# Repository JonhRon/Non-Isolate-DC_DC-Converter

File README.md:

# DC-DC Converter
The Project that i do with my 4th year at University.

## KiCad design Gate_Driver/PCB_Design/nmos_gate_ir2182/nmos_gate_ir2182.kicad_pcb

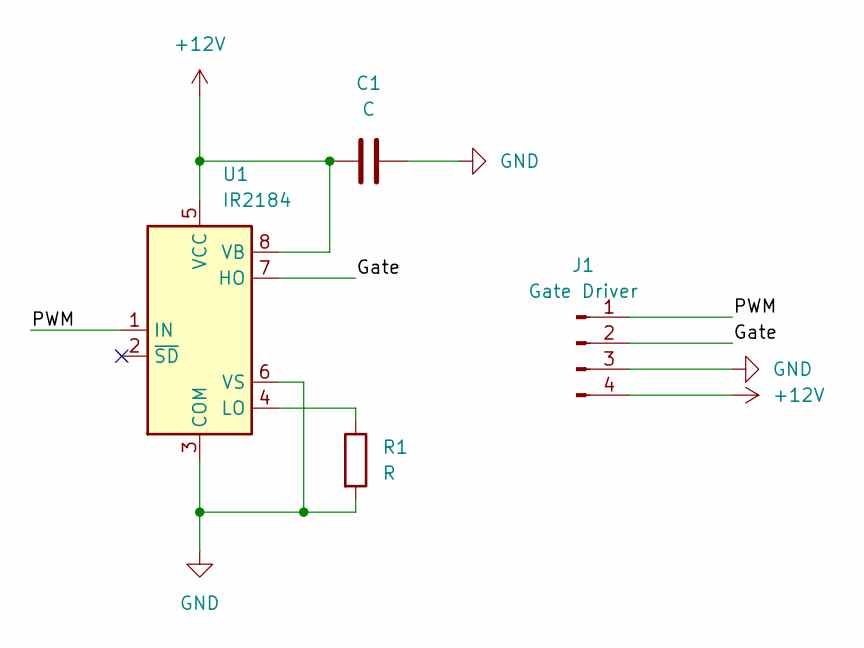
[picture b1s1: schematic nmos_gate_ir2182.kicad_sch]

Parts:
C1: C; C_0805_2012Metric_Pad1.18x1.45mm_HandSolder
J1: Gate Driver; PinHeader_1x04_P2.54mm_Vertical
R1: R; R_0805_2012Metric_Pad1.20x1.40mm_HandSolder
U1: IR2184; PowerIntegrations_SO-8

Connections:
+12V: C1.1, J1.4, U1.5 (VCC), U1.8 (VB)
/Gate: J1.2, U1.7 (HO)
/PWM: J1.1, U1.1 (IN)
GND: C1.2, J1.3, R1.2, U1.3 (COM), U1.6 (VS)
unnamed: R1.1, U1.4 (LO)

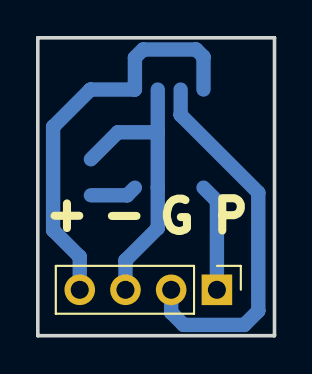
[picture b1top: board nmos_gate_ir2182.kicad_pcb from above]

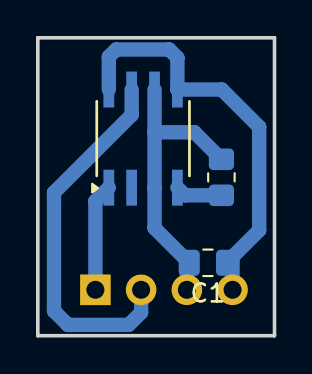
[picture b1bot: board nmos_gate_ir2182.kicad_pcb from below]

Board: 2 copper layers, 13.2 x 16.6 mm, 4 parts (3 on the bottom side), 5 nets.

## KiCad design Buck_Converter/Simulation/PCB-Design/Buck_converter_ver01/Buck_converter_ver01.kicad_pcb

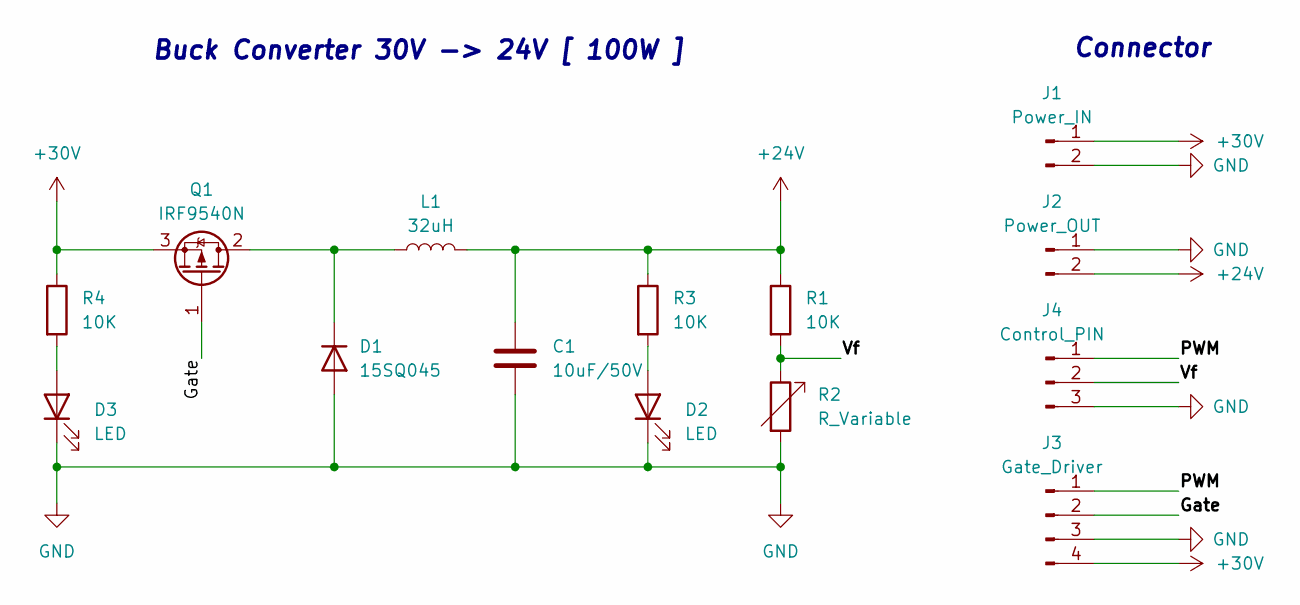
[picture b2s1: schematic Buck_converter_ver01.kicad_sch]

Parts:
C1: 10uF/50V; CP_Radial_D10.0mm_P3.50mm
D1: 15SQ045; D_P600_R-6_P12.70mm_Horizontal
D2, D3: LED; LED_D5.0mm
J1: Power_IN; TerminalBlock_bornier-2_P5.08mm
J2: Power_OUT; TerminalBlock_bornier-2_P5.08mm
J3: Gate_Driver; PinSocket_1x04_P2.54mm_Vertical
J4: Control_PIN; PinSocket_1x03_P2.54mm_Vertical
L1: 32uH; L_Wurth_WE-HCFT-2012_LeadDiameter1.5mm
Q1: IRF9540N; TO-220-3_Vertical
R1, R3, R4: 10K; R_0805_2012Metric_Pad1.20x1.40mm_HandSolder
R2: R_Variable; Potentiometer_Bourns_3296W_Vertical

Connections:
+24V: C1.1, J2.2, L1.2, R1.1, R3.1
+30V: J1.1, J3.4, Q1.3 (S), R4.1
/Gate: J3.2, Q1.1 (G)
/PWM: J3.1, J4.1
/Vf: J4.2, R1.2, R2.1
GND: C1.2, D1.2 (A), D2.1 (K), D3.1 (K), J1.2, J2.1, J3.3, J4.3, R2.2
unnamed: D1.1 (K), L1.1, Q1.2 (D)
unnamed: D2.2 (A), R3.2
unnamed: D3.2 (A), R4.2

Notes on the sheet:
Connector
Buck Converter 30V -> 24V [ 100W ]

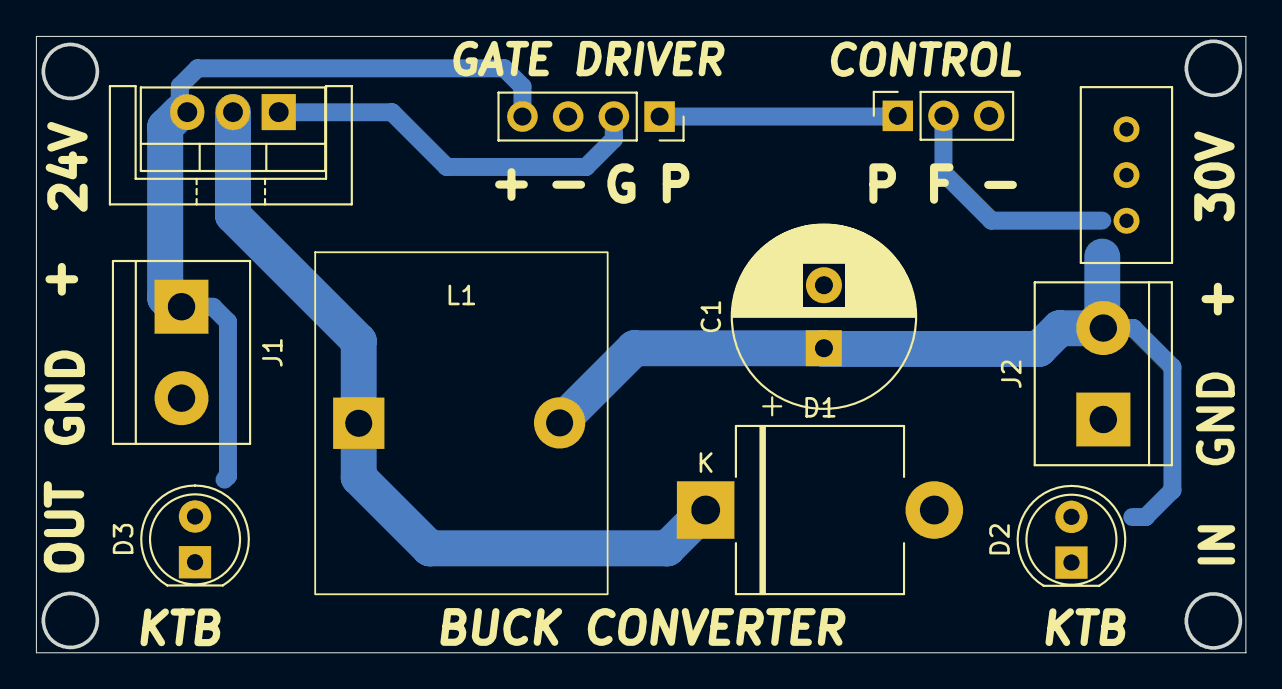
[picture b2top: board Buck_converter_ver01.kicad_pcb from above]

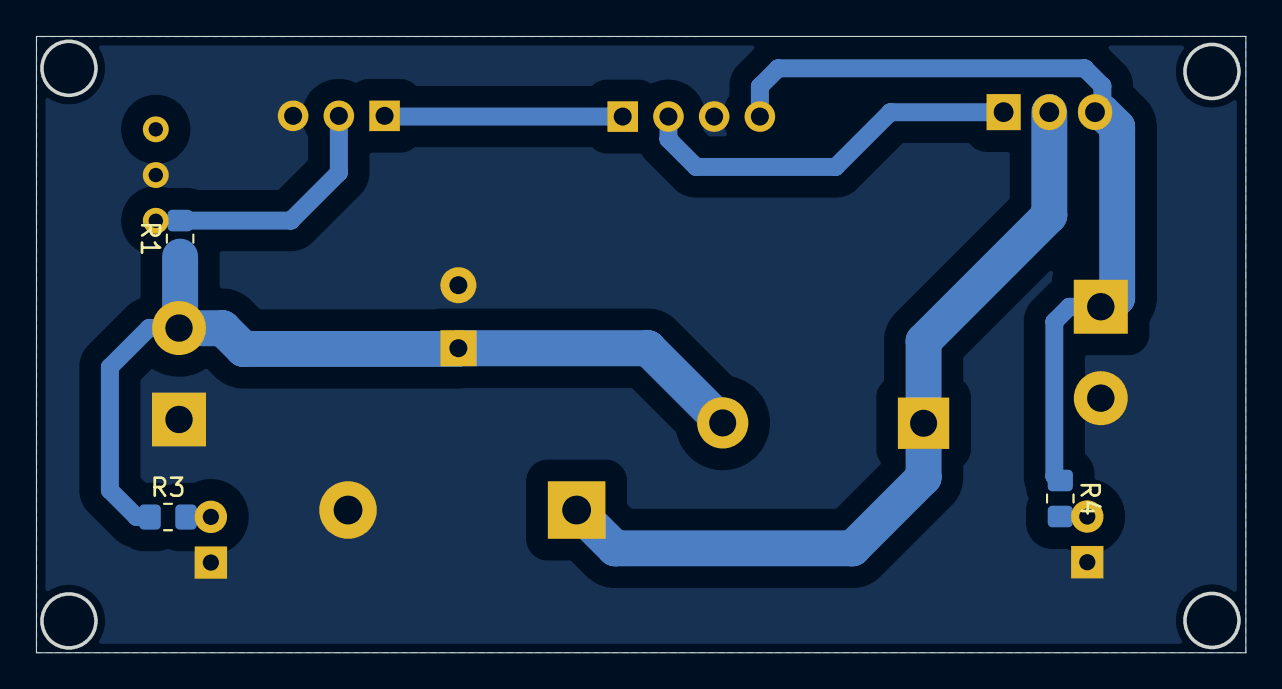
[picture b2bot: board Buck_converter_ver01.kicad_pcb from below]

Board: 2 copper layers, 67.2 x 34.2 mm, 14 parts (3 on the bottom side), 9 nets.

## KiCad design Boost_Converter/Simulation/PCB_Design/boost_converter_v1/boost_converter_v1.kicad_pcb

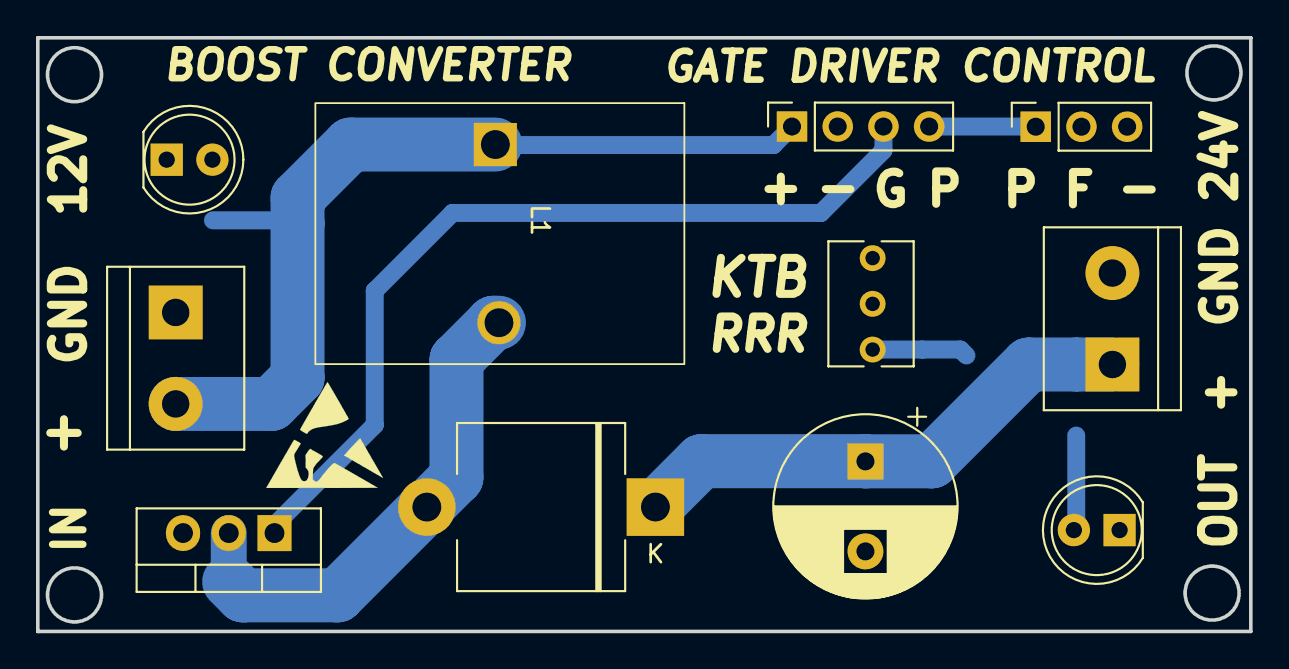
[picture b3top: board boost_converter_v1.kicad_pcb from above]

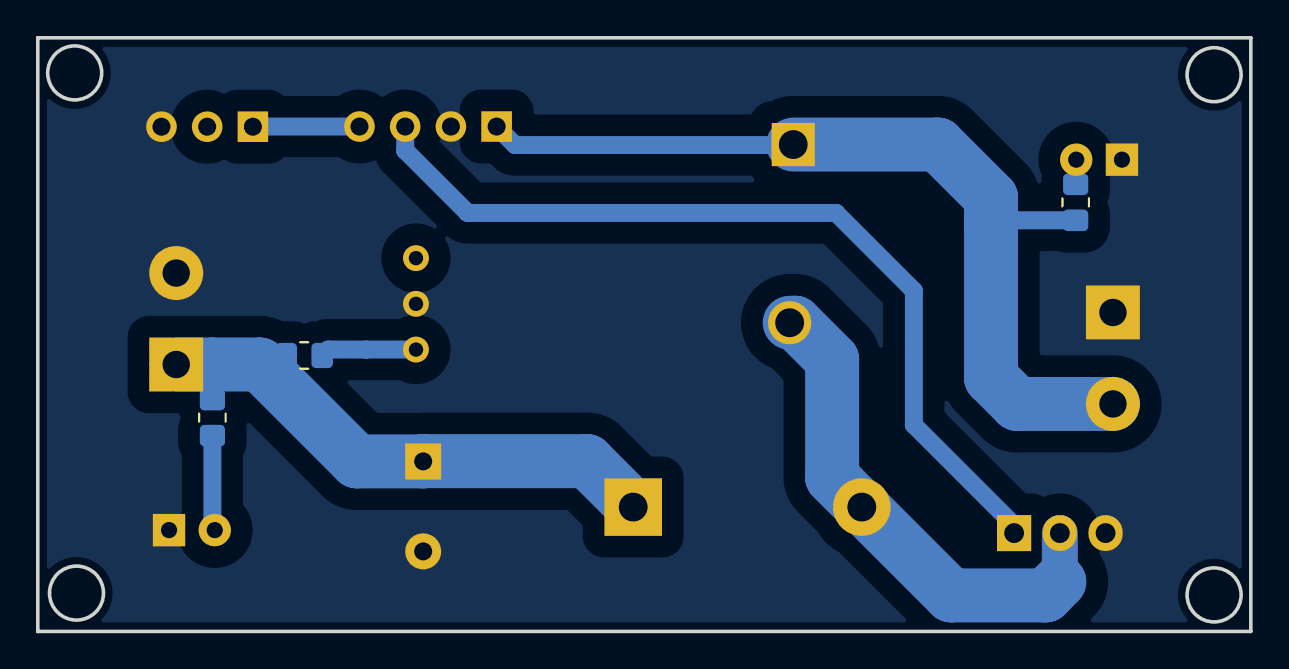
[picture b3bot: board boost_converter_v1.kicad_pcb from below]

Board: 2 copper layers, 67.4 x 33.0 mm, 14 parts (3 on the bottom side), 9 nets.

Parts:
C1: 100uF; CP_Radial_D10.0mm_P5.00mm
D1: 15SQ045; D_P600_R-6_P12.70mm_Horizontal
D2, D3: LED; LED_D5.0mm
J1: Power_IN; TerminalBlock_bornier-2_P5.08mm
J2: Power_OUT; TerminalBlock_bornier-2_P5.08mm
J3: Control; PinSocket_1x03_P2.54mm_Vertical
J4: Gate_Driver; PinSocket_1x04_P2.54mm_Vertical
L1: 20uH; L_Wurth_WE-HCFT-2012_LeadDiameter1.2mm
Q1: IRF540N; TO-220-3_Vertical
R1: 5K; R_0805_2012Metric_Pad1.20x1.40mm_HandSolder
R2, R3: 10K; R_0805_2012Metric_Pad1.20x1.40mm_HandSolder
R4: R_Variable; Potentiometer_Bourns_3266Y_Vertical

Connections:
+12V: J1.2, J4.1, L1.1, R1.1
+24V: C1.1, D1.1 (K), J2.1, R2.1, R3.1
/Gate: J4.3, Q1.1 (G)
/PWM: J3.1, J4.4
GND: C1.2, D2.1 (K), D3.1 (K), J1.1, J2.2, J3.3, J4.2, Q1.3 (S), R4.2
unnamed: D1.2 (A), L1.2, Q1.2 (D)
unnamed: D2.2 (A), R1.2
unnamed: D3.2 (A), R2.2
unnamed: R3.2, R4.1
